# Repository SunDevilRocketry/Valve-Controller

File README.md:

<h1>Valve Controller</h1>

<p>PCB Revision: 3.1</p>
<p>PCB Part No: L0005</p>
<p>The liquid engine's valve controller (L0005) contains the processor responsible for managing valve actuation commands issued by the liquid engine controller (L0002). The board contains opto-isolated solid state relays for solenoid actuation and a Pulse Width Modulation interface for issuing stepper motor commands that initiate actuation of the liquid engine's main propellant valves. The board contains an STM32H7 ARM Cortex-M7 microcontroller for processing, programmed using an STLink/V2 with a 20-pin IDC cable connection. The board is powered from the 5V buck converter on L0002, which is also used to power the photogate sensors used for valve position calibration. In order to allow the controller to know the true actuation state of the solenoids even in the event of a power failure, the board contains an AC power supply monitoring circuit which produces an indication signal read by the MCU when AC power is available for solenoid actuation. </p>

<p><b>Working Directory Structure:</b></p>

<p>
   cad: 3d models

   doc: documentation

   img: images of circuit/footprints for github display 

   lib: libraries for schematic symbols and footprints

   production: files needed for pcb fabrication, e.g. gerbers, profile, drill file

   sim: simulation models/files 

   src: source design files, e.g. schematic and PCB layout files
</p>

<h2>3D Model: </h2>

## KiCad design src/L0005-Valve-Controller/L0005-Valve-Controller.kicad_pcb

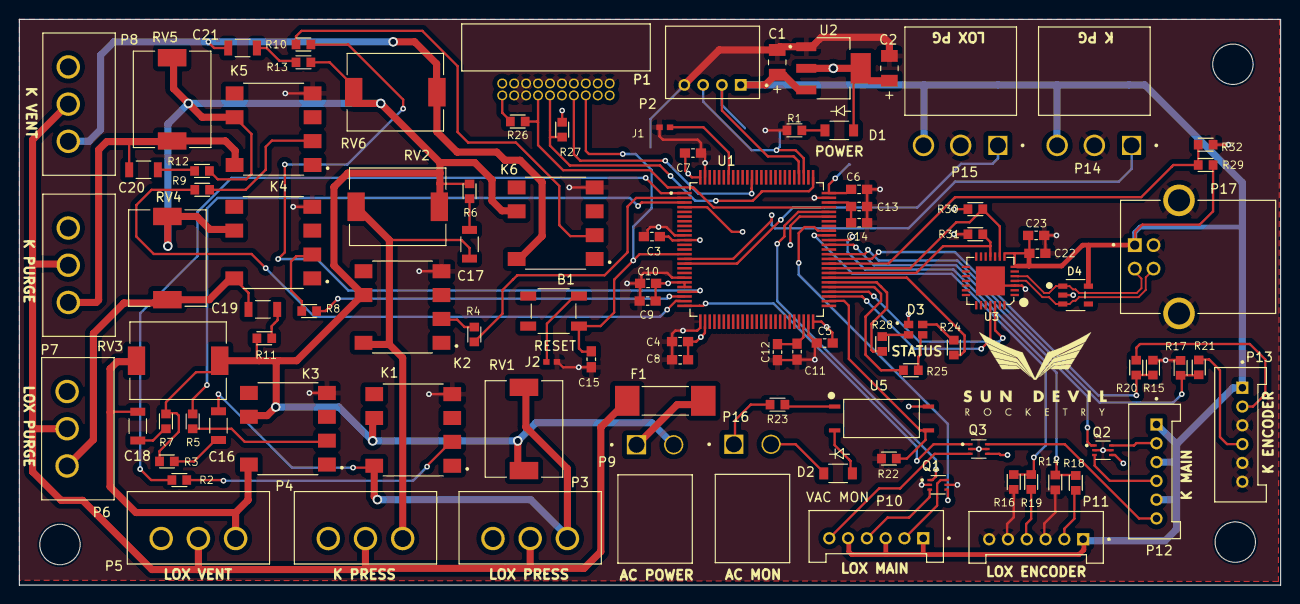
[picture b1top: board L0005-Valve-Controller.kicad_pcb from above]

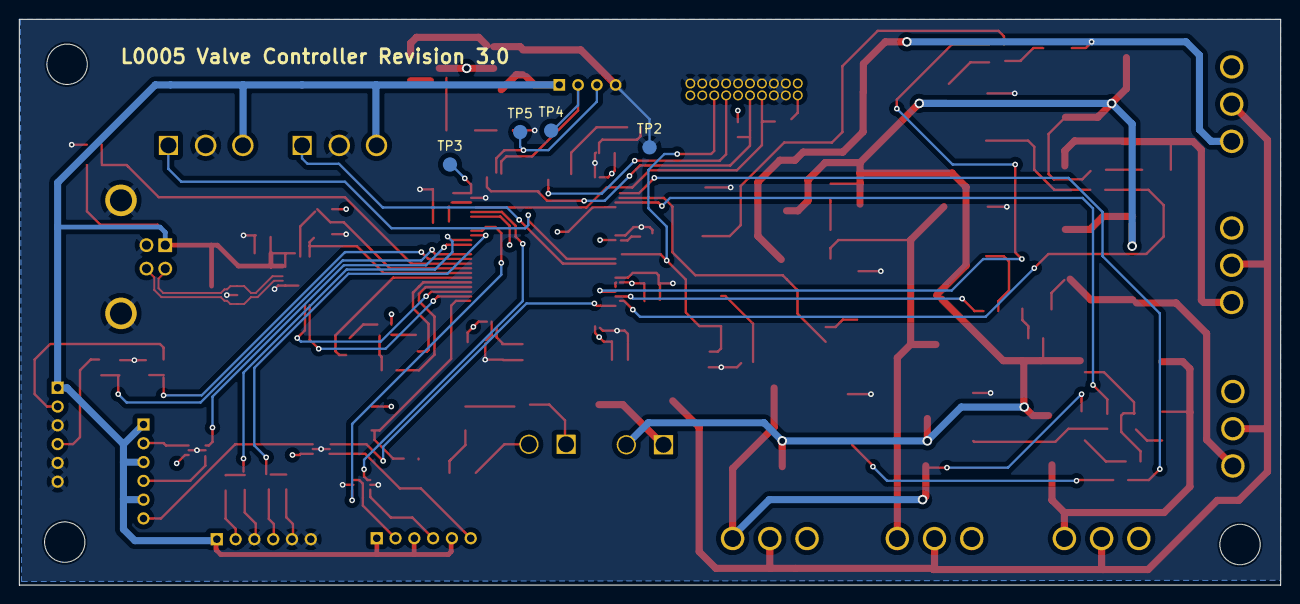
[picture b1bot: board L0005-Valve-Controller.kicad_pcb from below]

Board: 4 copper layers, 134.2 x 60.2 mm, 107 parts (4 on the bottom side), 81 nets.

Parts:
B1: PTS647SM38SMTR2LFS
C1, C2: 10uF; T491A106K010AT
C3, C4, C5, C6, C7, C10, C15, C23: 0.1uF; CAP_0603
C8: 4.7uF; CAP_0603
C9, C22: 1uF; CAP_0603
C11, C12, C13, C14: 2.2uF; CAP_0603
C16, C17, C18, C19, C20, C21: 0.1uF; CAP_1206
D1, D2: LED_GREEN; SML-LX1206GC-TR
D3: CLMVC-FKA-CL1D1L71BB7C3C3
D4: SP0504BAHTG
F1: 0678L9100-02; FUSC9830X318N
H1, H2, H3: Mounting-Hole; MountingHole_4.3mm_M4_DIN965
J1, J2: Jumper_NO; Jumper-NO
K1, K2, K3, K4, K5, K6: AQH0223AX; RELAY_AQH0223AX
LOGO1: Logo
P1: 3220-20-0200-00
P2: 140-504-415-000
P3, P4, P5, P6, P7, P8: 647676-3; 353130360
P9, P16: 647676-2; TE_647676-2
P10, P11, P12, P13: 353620650; MOLEX_35362-0650
P14, P15: 647676-3
P17: USB; USB-TypeB
Q1, Q2, Q3: CMLDM7003; CMLDM7003 TR
R1: 240; RES_0603
R2, R3, R4, R5, R6, R7, R8, R9, R10, R11, R12, R13: 100; RES_0603
R14, R15, R16, R17, R22, R29, R31: 10k; RES_0603
R18, R19, R20, R21: 1k; RES_0603
R23: 5k; RES_0603
R24: 68; RES_0603
R25: 82; RES_0603
R26, R27: 100k; RES_0603
R28: 280; RES_0603
R30: 4.7k; RES_0603
R32: 20k; RES_0603
RV1, RV2, RV3, RV4, RV5, RV6: 275V; PV275K4032R2
TP2, TP3, TP4, TP5: TP
U1: STM32H750VBTx; STM32H750VBT6
U2: LMS8117AMP-3.3_NOPB; LMS8117AMP-3.3NOPB
U3: CP2102-GMR(QFN28); CP2012-GMR
U5: Optocoupler; Opto_140105146000

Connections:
3.3V: C2.1, C3.2, C4.2, C5.2, C6.2, C7.2, C8.2, C9.2, C10.2, D1.2, D3.1, P1.1, P1.2, R26.2, R27.2, R30.1, TP3.1, U1.11 (VDD), U1.20 (VREF+), U1.21 (VDDA), U1.27 (VDD), U1.50 (VDD), U1.75 (VDD), U1.100 (VDD), U2.2 (VOUT), U5.4
5V: C1.1, C22.1, C23.1, D4.5, P2.1 (+12V), P10.1 (+12V), P10.3, P10.5, P11.1 (+12V), P12.1 (+12V), P12.3, P12.5, P13.1 (+12V), P14.3, P15.3, P17.1 (VCC), R29.2, U2.3 (VIN), U3.7 (REGIN), U3.8 (VBUS)
/Power/D+: D4.3, P17.3 (D+), U3.4 (D+)
/Power/D-: D4.1, P17.2 (D-), U3.5 (D-)
AC_HOT: F1.1, P3.2, P4.2, P5.2, P6.2, P7.2, P8.2
AC_NEUTRAL: K1.6, K2.6, K3.6, K4.6, K5.6, K6.6, P9.2, R3.2, R6.2, R7.2, R11.2, R12.2, R13.2, RV1.2, RV2.2, RV3.2, RV4.2, RV5.2, RV6.2
BOOT: J1.1 (A), U1.94 (BOOT0)
ENCD1_A: R14.1, R18.1, U1.65 (PC8)
ENCD1_B: R16.1, R19.2, U1.66 (PC9)
ENCD2_A: R15.1, R20.1, U1.61 (PD14)
ENCD2_B: R17.1, R21.2, U1.62 (PD15)
Earth: C1.2, C2.2, C3.1, C4.1, C5.1, C6.1, C7.1, C8.1, C9.1, C10.1, C11.1, C12.1, C13.1, C14.1, C15.2, C22.2, C23.2, D4.2, J1.2 (B), J2.1 (A), K1.4, K2.4, K3.4, K4.4, K5.4, K6.4, P1.3, P1.4, P1.5, P1.6, P1.8, P1.10, P1.12, P1.14, P1.16, P1.18, P1.20, P2.4, P11.3, P11.5, P11.6, P13.3, P13.5, P13.6, P14.2, P15.2, P17.4 (GND), P17.S1 (SHIELD), P17.S2 (SHIELD), Q1.2 (S), Q1.5 (S), Q2.2 (S), Q2.5 (S), Q3.2 (S), Q3.5 (S), R1.1, R14.2, R15.2, R16.2, R17.2, R22.2, R31.1, R32.1, TP2.1, U1.10 (VSS), U1.19 (VSSA), U1.26 (VSS), U1.49 (VSS), U1.74 (VSS), U1.99 (VSS), U2.1 (GND), U3.3 (GND), U3.29 (PAD)
NRST: B1.1, C15.1, P1.15, U1.14 (NRST)
unnamed: C16.1, R3.1
unnamed: C16.2, K1.8, P3.1, RV1.1
unnamed: C17.1, R6.1
unnamed: C17.2, K2.8, P4.1, RV2.1
unnamed: C18.1, R7.1
unnamed: C18.2, K3.8, P5.1, RV3.1
unnamed: C19.1, R11.1
unnamed: C19.2, K4.8, P6.1, RV4.1
unnamed: C20.1, R12.1
unnamed: C20.2, K5.8, P7.1, RV5.1
unnamed: C21.1, R13.1
unnamed: C21.2, K6.8, P8.1, RV6.1
unnamed: D1.1, R1.2
unnamed: D2.1, P16.2
unnamed: D2.2, U5.2
unnamed: D3.2, R24.2
unnamed: D3.3, R25.2
unnamed: D3.4, R28.2
unnamed: F1.2, P9.1
unnamed: B1.3, J2.2 (B)
unnamed: K1.2, R2.2
unnamed: K2.2, R4.2
unnamed: K3.2, R5.2
unnamed: K4.2, R8.2
unnamed: K5.2, R9.2
unnamed: K6.2, R10.2
unnamed: P11.2 (GND), R18.2
unnamed: P11.4, R19.1
unnamed: P13.2 (GND), R20.2
unnamed: P13.4, R21.1
unnamed: P16.1, R23.2
unnamed: R23.1, U5.1
PG1: P14.1, U1.15 (PC0)
PG2: P15.1, U1.16 (PC1)
RX: P2.2 (GND), TP4.1, U1.79 (PC11)
RX_USB: U1.53 (PB14), U3.25 (RXD)
SBV1_DIR: Q1.1 (G), U1.71 (PA12)
SBV1_DIR-: P10.2 (GND), Q1.6 (D)
SBV1_EN: Q1.4 (G), U1.67 (PA8)
SBV1_EN-: P10.4, Q1.3 (D)
SBV1_PUL: Q3.4 (G), U1.4 (PE5)
SBV1_PUL-: P10.6, Q3.3 (D)
SBV2_DIR: Q2.1 (G), U1.64 (PC7)
SBV2_DIR-: P12.2 (GND), Q2.6 (D)
SBV2_EN: Q2.4 (G), U1.70 (PA11)
SBV2_EN-: P12.4, Q2.3 (D)
SBV2_PUL: Q3.1 (G), U1.25 (PA3)
SBV2_PUL-: P12.6, Q3.6 (D)
SOL1: R2.1, U1.1 (PE2)
SOL2: R4.1, U1.2 (PE3)
SOL3: R5.1, U1.3 (PE4)
SOL4: R10.1, U1.22 (PA0)
SOL5: R8.1, U1.23 (PA1)
SOL6: R9.1, U1.24 (PA2)
STATUS_B: R24.1, U1.57 (PD10)
STATUS_G: R25.1, U1.55 (PD8)
STATUS_R: R28.1, U1.56 (PD9)
SWCLK: P1.9, R27.1, U1.76 (PA14)
SWDIO: P1.7, R26.1, U1.72 (PA13)
SWO: P1.13, U1.89 (PB3)
TX: P2.3, TP5.1, U1.78 (PC10)
TX_USB: U1.54 (PB15), U3.26 (TXD)
USB_DETECT: R29.1, R32.2, U1.60 (PD13)
VAC_MON: R22.1, U1.52 (PB13), U5.3
VCAP1: C11.2, C12.2, U1.48 (VCAP1)
VCAP2: C13.2, C14.2, U1.73 (VCAP2)
~USB_RST: R30.2, U1.59 (PD12), U3.9 (~RST)
~USB_SUSPEND: R31.2, U1.58 (PD11), U3.11 (~SUSPEND)

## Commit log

2021-12-14 Added details to README file
2021-12-15 Created directory structure
2021-12-15 Started lib files and added MCU
2021-12-18 Added SSR to lib files
2021-12-18 Added 0603 resistor to lib files
2021-12-18 Added 1206 capacitor to lib files
2021-12-18 Added varistor to lib files
2021-12-18 Restore original README
2021-12-18 Updated README with documentation description
2021-12-21 Added programming connector to lib files
2021-12-23 Added connectors to lib files
2021-12-23 Added optocoupler to lib files
2021-12-24 Added level shifter to lib files
2021-12-24 Added LED to lib files
2021-12-24 Added Button to lib files
2021-12-24 Added 0603 cap to lib files
2021-12-25 Added NXP MCU to lib files
2021-12-25 Added MCU power decoupling to schematic
2021-12-26 Added programmer to schematic
2021-12-26 Added power supply to schematic
2021-12-26 Added UART interface to schematic
2021-12-26 Added SSR Solenoid drivers to schematic
2021-12-26 Added AC source to schematic
2021-12-26 Added servo-actuated ball valves to schematic
2021-12-26 Added fuse to lib files
2021-12-27 added simulation for rectifier
2021-12-27 Added Red LED to lib files
2021-12-28 Added MCU control signals
2021-12-28 Added test points
2021-12-28 routed MCU power decoupling
2021-12-28 routed solenoid SSRs
2021-12-28 finished controller routing
2022-01-07 fixed SWD schematic connections for J-Link
2022-01-08 moved stepper circuits to second schematic sheet
2022-01-09 inverted VAC_MON signal
2022-01-09 wrote python script to calculate NMOS current
2022-01-09 Added NMOS array to lib files
2022-01-09 Added 5V open drain logic to stepper motor control signals
2022-01-09 Rearranged schematic
2022-01-09 ploted schematic capture to pdf
2022-01-09 changed LED current limiters to 470 Ohm
2022-01-09 replotted schematic with updated LED resistor values
2022-01-10 rerouted PCB to include 5V logic MOSFETS
2022-01-10 fixed kicad glitch
2022-01-10 produced gerbers files
2022-01-10 Fixed error with regulator routimg
2022-01-28 Added more detail to readme description
2022-01-29 Corrected README detail regarding main valve actuation
2022-01-29 Added description of AC supply monitoring to README.mf
2022-01-29 Added pcb part number info to readme
2022-01-29 Added outline structure to README
2022-01-29 added PCB image to README
2022-01-29 fixed img bug in readme
2022-01-29 Added back view of 3D model to README
2022-01-29 Added schematic images to readme
2022-01-29 replaced readme MCU schematic
2022-01-29 removed old readme schematic
2022-01-29 Added AC monitoring schematic to readme
2022-01-29 fixed issue with AC monitoring image file path in reademe
2022-04-10 added new STM32 MCU to lib files
2022-04-10 added decoder to lib files
2022-04-11 added solenoid control decoder
2022-04-11 added 2:4 decoder to lib files
2022-04-11 added STM32H7 MCU
2022-04-12 updated schematic with STM32H7 MCU
2022-04-12 plotted schematic to pdf
2022-04-13 routed rev 2
2022-04-13 zipped rev2 gerbers
2022-05-07 updated pcb rev number on readme
2022-05-07 updated 3d view images for rev 2
2022-05-07 updated readme mcu schematic
2022-06-30 fixed 3D model paths
2022-07-02 added 3D model for rev 2.0
2023-03-09 kicad backups
2023-03-09 added NO jumper to MCU reset button
2023-03-09 changed level shifter to opendrain mosfet for pulse interface
2023-03-09 added USB to lib files and schematic
2023-03-10 finalized schematic
2023-03-10 routed rev3
2023-04-08 generated rev3 step file
2023-06-10 fixed photogate pinouts to allow for straight cable to photogate connector
2023-06-10 updated readme to rev 3.1
2023-06-10 fixed filename of readme 3D model image

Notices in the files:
parts and their libraries:
Copyright 2021 Accelerated Designs. All rights reserved.
